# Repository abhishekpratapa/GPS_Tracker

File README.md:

# GPS_Tracker
A GPS tracker for a 3rd party logistics company. A medium article on how it came to be:<br/> https://medium.com/abhishek-pratapa/the-gps-tracker-842071f3ebae#.iqlriwf8i

<h2>Software</h2>

The software of the tracker consisted of an Arduino sketch and a backend initially built in Node.js however we scrapped that after we didn't have the funds to pay for the twillio api access.<br/>

<h2>Hardware</h2>

The hardware of the tracker consisted of the below components, a full listing of parts is to follow later. <br/>

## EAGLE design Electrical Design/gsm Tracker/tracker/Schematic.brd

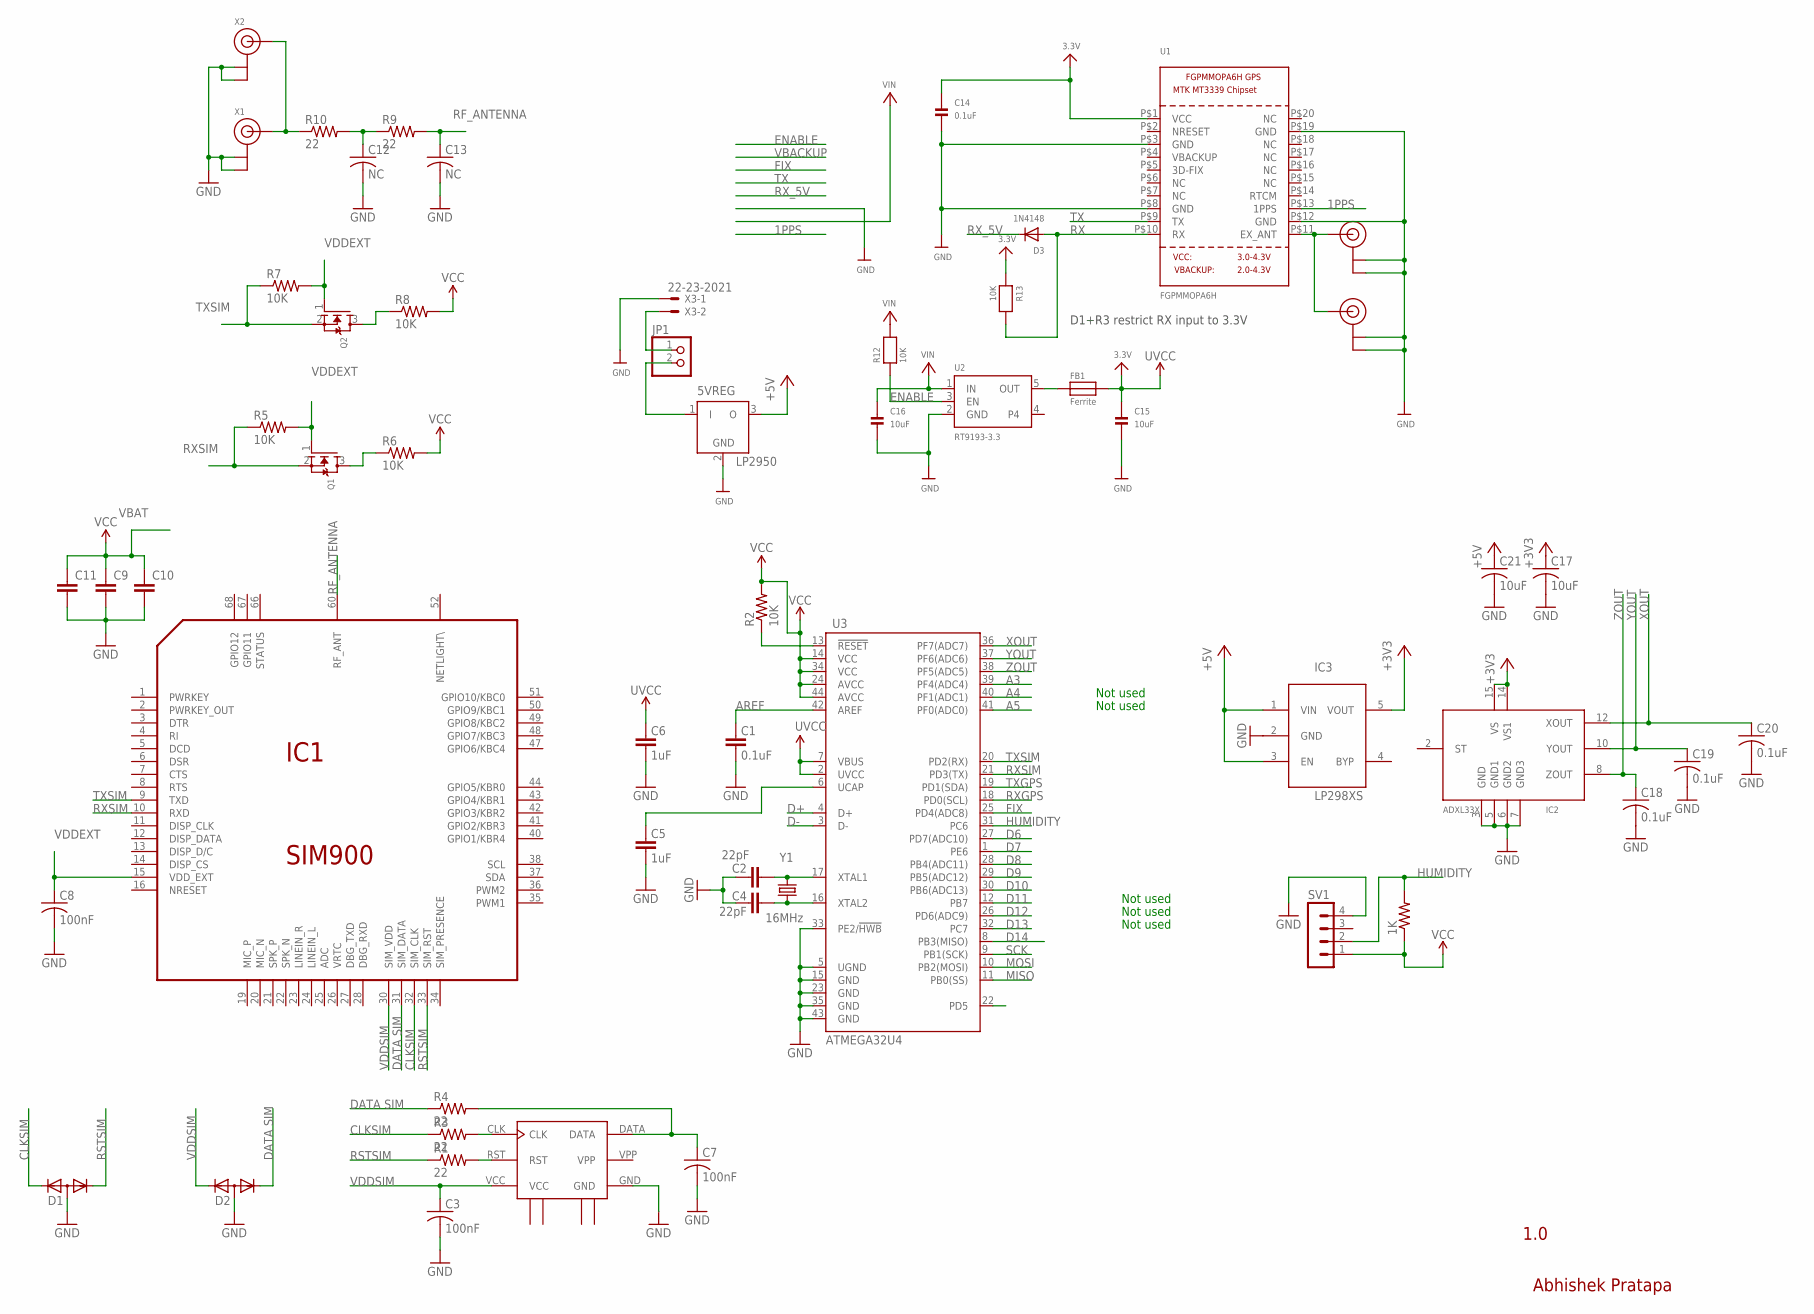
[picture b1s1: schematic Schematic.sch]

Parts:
1K: R-US_M0805; M0805
5VREG: LP2950; DPACK
C1: 0.1uF; 0603-CAP
C2, C4: 22pF; 0603-CAP
C3, C7, C8: 100nF; C0805
C5, C6: 1uF; 0603-CAP
C9, C10, C11: C-EUC0805; C0805
C12, C13: NC; C0805
C14: 0.1uF; 0805
C15, C16: 10uF; 0805
C17, C21: 10uF; C0805K
C18, C19, C20: 0.1uF; C0805K
D1, D2: DIODE-2CA|ACSOT23; SOT23
D3: 1N4148; SOD-323F
FB1: Ferrite; 0805
IC1: SIM900
IC2: ADXL33X; 16LCSP
IC3: LP298XS; SOT23-5L
JP1: PINHD-1X2; 1X02
Q1, Q2: MOSFET-NREFLOW; SOT23
R1, R3, R4: 22; M0805
R2: 10K; 0603-RES
R5, R6, R7, R8: 10K; M0805
R9, R10: 22; R0805
R12, R13: 10K; 0805
SV1: MA04-1
U1: FGPMMOPA6H
U2: RT9193-3.3; SOT23-5
U3: ATMEGA32U4; QFN-44-NOPAD_1:1-OUTFAKES
U$1: SCU-W0822XR-06
U$8, U$20: U.FL
X1, X2: ANTENNA_U.FL; U.FL
X3: 22-23-2021
Y1: 16MHz; CRYSTAL-SMD-5X3

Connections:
1PPS: U1.P$13 (1PPS)
3.3V: 1K.1, C14.1, C15.1, FB1.2, R13.1, SV1.1, U1.P$1 (VCC)
+3V3: C17.1, IC2.14 (VS1), IC2.15 (VS), IC3.5 (VOUT)
+5V: 5VREG.3 (O), C21.1, IC3.1 (VIN), IC3.3 (EN)
A3: U3.39 (PF4(ADC4))
A4: U3.40 (PF1(ADC1))
A5: U3.41 (PF0(ADC0))
AREF: C1.2, U3.42 (AREF)
CLKSIM: D1.2 (K2), IC1.32 (SIM_CLK), R3.1
D6: U3.27 (PD7(ADC10))
D7: U3.1 (PE6)
D8: U3.28 (PB4(ADC11))
D9: U3.29 (PB5(ADC12))
D10: U3.30 (PB6(ADC13))
D11: U3.12 (PB7)
D12: U3.26 (PD6(ADC9))
D13: U3.32 (PC7)
D14: U3.8 (PB3(MISO))
D+: U3.4 (D+)
D-: U3.3 (D-)
DATASIM: D2.1 (K1), IC1.31 (SIM_DATA), R4.1
ENABLE: R12.1, U2.3 (EN)
FIX: U3.25 (PD4(ADC8))
GND: 5VREG.2 (GND), C1.1, C2.2, C3.2, C4.2, C5.1, C6.1, C7.2, C8.2, C9.2, C10.2, C11.2, C12.2, C13.2, C14.2, C15.2, C16.2, C17.2, C18.2, C19.2, C20.2, C21.2, D1.3 (A), D2.3 (A), IC1.17 (GND), IC1.18 (GND), IC1.29 (GND), IC1.39 (GND), IC1.45 (GND), IC1.46 (GND), IC1.53 (GND), IC1.54 (GND), IC1.58 (GND), IC1.59 (GND), IC1.61 (GND), IC1.62 (GND), IC1.63 (GND), IC1.64 (GND), IC1.65 (GND), IC2.3 (GND), IC2.5 (GND1), IC2.6 (GND2), IC2.7 (GND3), IC3.2 (GND), SV1.4, U1.P$3 (GND), U1.P$8 (GND), U1.P$12 (GND), U1.P$19 (GND), U2.2 (GND), U3.5 (UGND), U3.15 (GND), U3.23 (GND), U3.33 (PE2/!HWB), U3.35 (GND), U3.43 (GND), U$1.GND, U$1.GND_1 (GND1), U$1.GND_2 (GND2), U$1.GND_3 (GND3), U$8.P$1 (GND), U$8.P$2 (GND), U$20.P$1 (GND), U$20.P$2 (GND), X1.1 (GND), X1.2 (GND), X2.1 (GND), X2.2 (GND), X3.1
GND4: U$1.GND_4 (GND4)
HUMIDITY: 1K.2, SV1.2, U3.31 (PC6)
MISO: U3.11 (PB0(SS))
MOSI: U3.10 (PB2(MOSI))
unnamed: C4.1, U3.16 (XTAL2), Y1.1
unnamed: C2.1, U3.17 (XTAL1), Y1.3 (2)
unnamed: R1.2, U$1.RST
unnamed: C5.2, U3.6 (UCAP)
unnamed: R3.2, U$1.CLK
unnamed: C7.1, R4.2, U$1.DATA
unnamed: R10.1, X1.3 (SIGNAL), X2.3 (SIGNAL)
unnamed: C12.1, R9.1, R10.2
unnamed: Q1.3 (D), R6.1
unnamed: Q2.3 (D), R8.1
unnamed: 5VREG.1 (I), JP1.2
unnamed: FB1.1, U2.5 (OUT)
unnamed: U1.P$11 (EX_ANT), U$8.P$3 (SIGNAL), U$20.P$3 (SIGNAL)
unnamed: JP1.1, X3.2
RESET: R2.1, U3.13 (!RESET)
RF_ANTENNA: C13.1, IC1.60 (RF_ANT), R9.2
RSTSIM: D1.1 (K1), IC1.33 (SIM_RST), R1.1
RX: D3.A, R13.2, U1.P$10 (RX)
RXSIM: IC1.10 (RXD), Q1.2 (S), R5.1, U3.21 (PD3(TX))
RX_5V: D3.C, U3.18 (PD0(SCL))
SCK: U3.9 (PB1(SCK))
TX: U1.P$9 (TX), U3.19 (PD1(SDA))
TXLED: U3.22 (PD5)
TXSIM: IC1.9 (TXD), Q2.2 (S), R7.1, U3.20 (PD2(RX))
UVCC: C6.2, U3.2 (UVCC), U3.7 (VBUS)
VBAT: IC1.55 (VBAT), IC1.56 (VBAT), IC1.57 (VBAT)
VCCSIM: C3.1, D2.2 (K2), IC1.30 (SIM_VDD), U$1.VCC
VDDEXT: C8.1, IC1.15 (VDD_EXT), Q1.1 (G), Q2.1 (G), R5.2, R7.2
VIN: C9.1, C10.1, C11.1, C16.1, R2.2, R6.2, R8.2, R12.2, U2.1 (IN), U3.14 (VCC), U3.24 (AVCC), U3.34 (VCC), U3.44 (AVCC)
VPP: U$1.VPP
XOUT: C20.1, IC2.12 (XOUT), U3.36 (PF7(ADC7))
YOUT: C19.1, IC2.10 (YOUT), U3.37 (PF6(ADC6))
ZOUT: C18.1, IC2.8 (ZOUT), U3.38 (PF5(ADC5))

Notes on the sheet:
Not used
DATA SIM
VDDSIM
CLKSIM
RSTSIM
VBAT
D1+R3 restrict RX input to 3.3V
TXGPS
RXGPS
Abhishek Pratapa
1.0

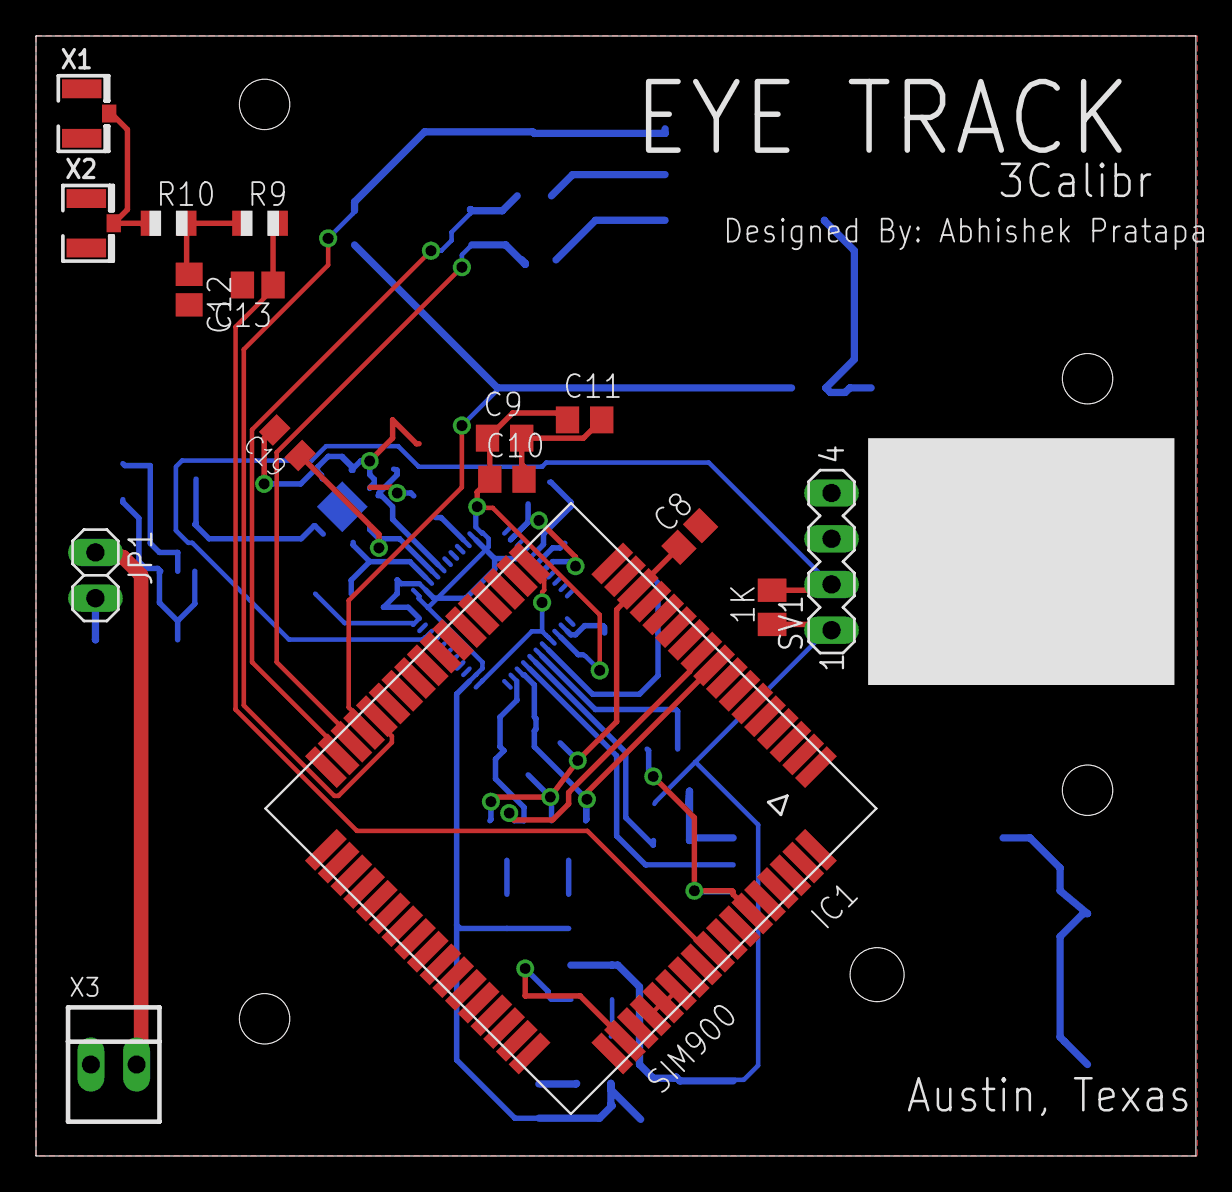
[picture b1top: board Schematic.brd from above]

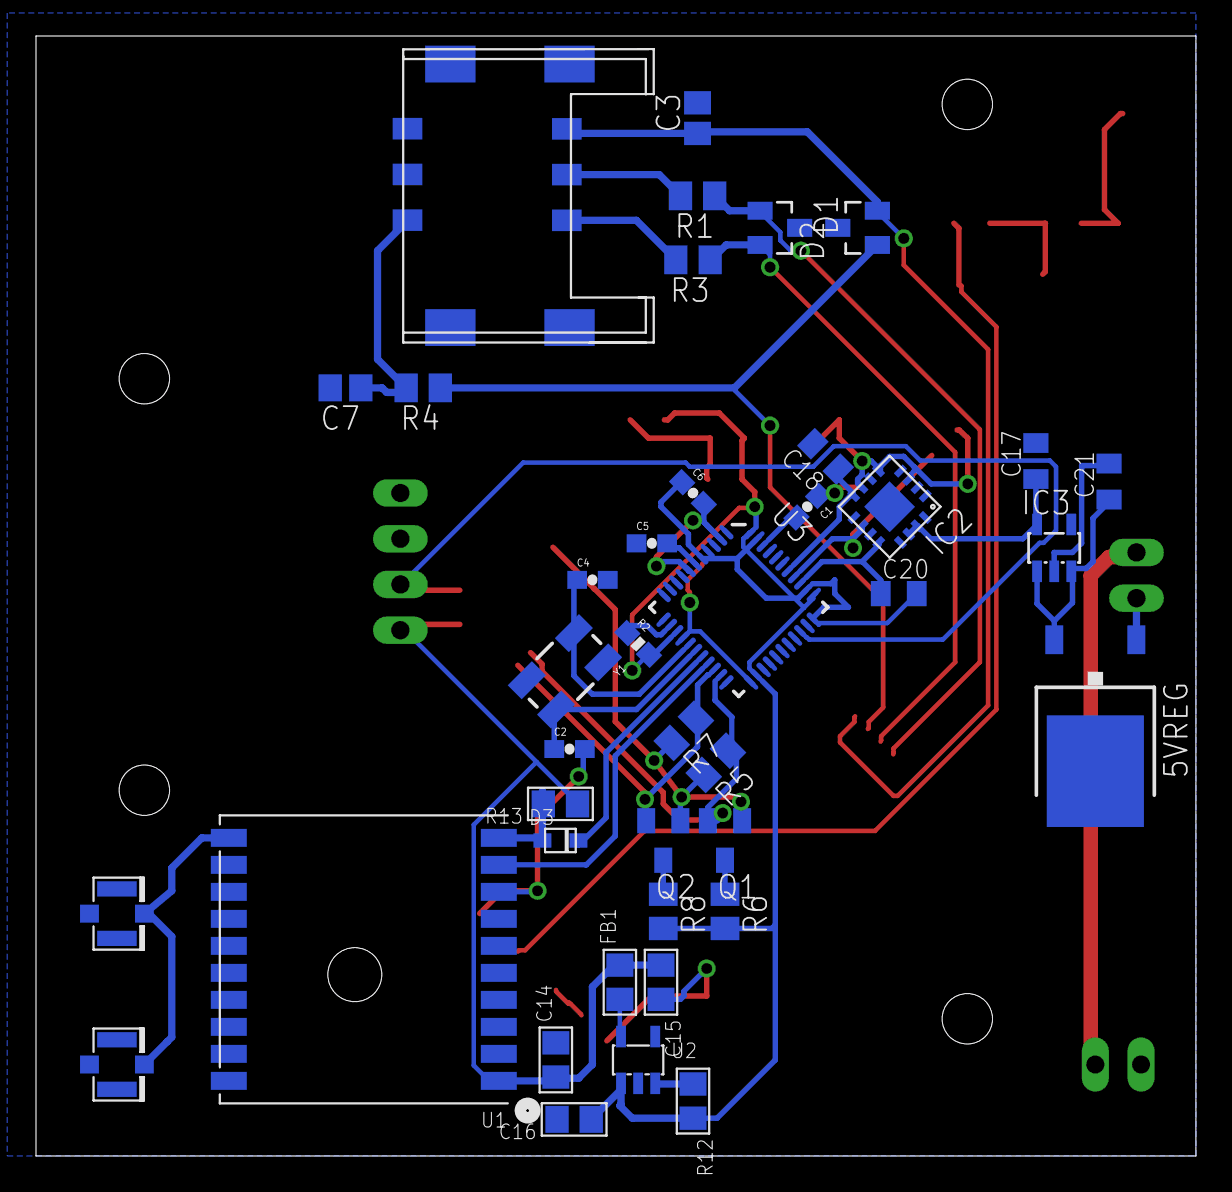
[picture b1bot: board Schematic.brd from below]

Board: 2 copper layers, 64.4 x 62.2 mm, 56 parts (40 on the bottom side), 39 nets.

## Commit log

2016-06-18 Added Arduino Code
2016-06-18 pictures
